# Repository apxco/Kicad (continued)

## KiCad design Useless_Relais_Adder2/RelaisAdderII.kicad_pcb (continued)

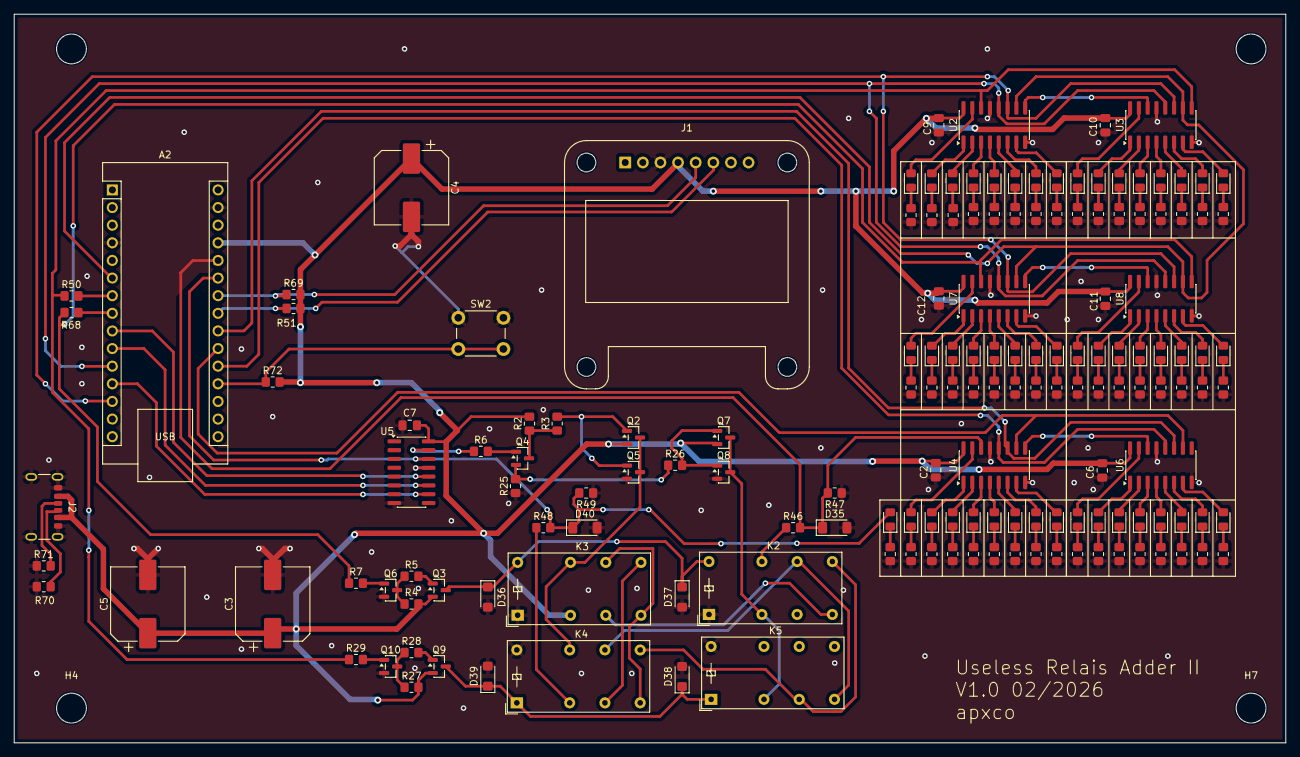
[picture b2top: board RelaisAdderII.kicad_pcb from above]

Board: 2 copper layers, 183.2 x 105.0 mm, 164 parts (0 on the bottom side), 145 nets.

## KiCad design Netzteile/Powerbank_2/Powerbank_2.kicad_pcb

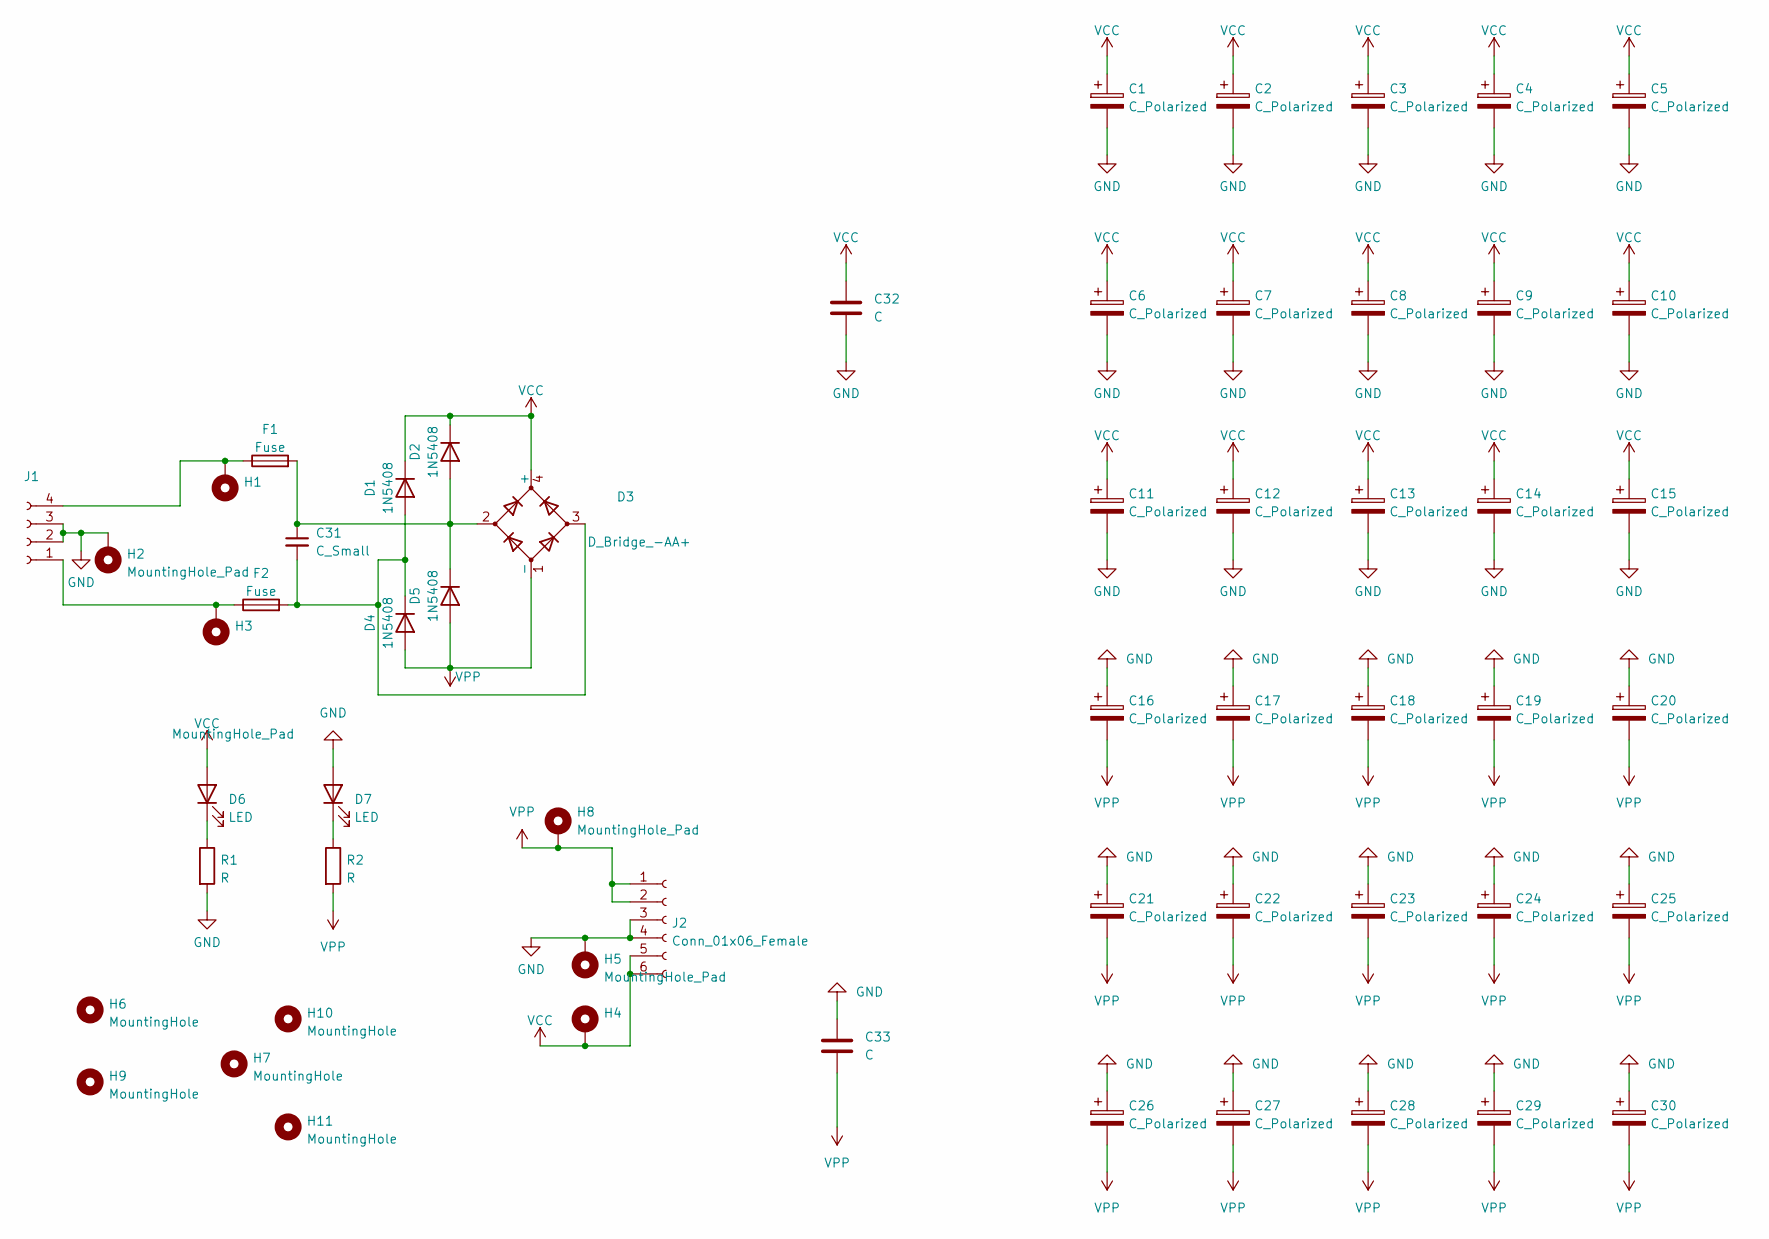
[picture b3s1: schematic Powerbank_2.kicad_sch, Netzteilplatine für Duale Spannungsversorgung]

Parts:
C1, C2, C3, C4, C5, C6, C7, C8, C9, C10, C11, C12, C13, C14, C15, C16, C17, C18, C19, C20, C21, C22, C23, C24, C25, C26, C27, C28, C29, C30: C_Polarized; CP_Radial_D10.0mm_P5.00mm_P7.50mm
C31: C_Small; C_Axial_L12.0mm_D6.5mm_P15.00mm_Horizontal
C32, C33: C; C_Rect_L16.5mm_W5.0mm_P15.00mm_MKT
D1, D2, D4, D5: 1N5408; D_DO-201AD_P15.24mm_Horizontal
D3: D_Bridge_-AA+; Diode_Bridge_Vishay_GBU
D6, D7: LED; LED_D3.0mm_Clear
F1, F2: Fuse; Fuseholder_Littelfuse_100_series_5x20mm
H1, H2, H3, H4, H5, H8: MountingHole_Pad; MountingHole_3.2mm_M3_Pad_TopBottom
H6, H7, H9, H10, H11: MountingHole; MountingHole_3.5mm_Pad
J1: Conn_01x04_Female; TerminalBlock_RND_205-00278_1x04_P5.00mm_Vertical
J2: Conn_01x06_Female; TerminalBlock_RND_205-00060_1x06_P5.00mm_45Degree
R1, R2: R; R_Axial_DIN0204_L3.6mm_D1.6mm_P7.62mm_Horizontal

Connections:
GND: C1.2, C2.2, C3.2, C4.2, C5.2, C6.2, C7.2, C8.2, C9.2, C10.2, C11.2, C12.2, C13.2, C14.2, C15.2, C16.1, C17.1, C18.1, C19.1, C20.1, C21.1, C22.1, C23.1, C24.1, C25.1, C26.1, C27.1, C28.1, C29.1, C30.1, C32.2, C33.1, D7.2 (A), H2.1, H5.1, J1.2, J1.3, J2.3, J2.4, R1.2
unnamed: C31.2, D1.2 (A), D3.3, D4.1 (K), F2.2
unnamed: C31.1, D2.2 (A), D3.2, D5.1 (K), F1.2
unnamed: D6.1 (K), R1.1
unnamed: D7.1 (K), R2.1
unnamed: F2.1, H3.1, J1.1
unnamed: F1.1, H1.1, J1.4
VCC: C1.1, C2.1, C3.1, C4.1, C5.1, C6.1, C7.1, C8.1, C9.1, C10.1, C11.1, C12.1, C13.1, C14.1, C15.1, C32.1, D1.1 (K), D2.1 (K), D3.4 (+), D6.2 (A), H4.1, J2.5, J2.6
VPP: C16.2, C17.2, C18.2, C19.2, C20.2, C21.2, C22.2, C23.2, C24.2, C25.2, C26.2, C27.2, C28.2, C29.2, C30.2, C33.2, D3.1 (-), D4.2 (A), D5.2 (A), H8.1, J2.1, J2.2, R2.2

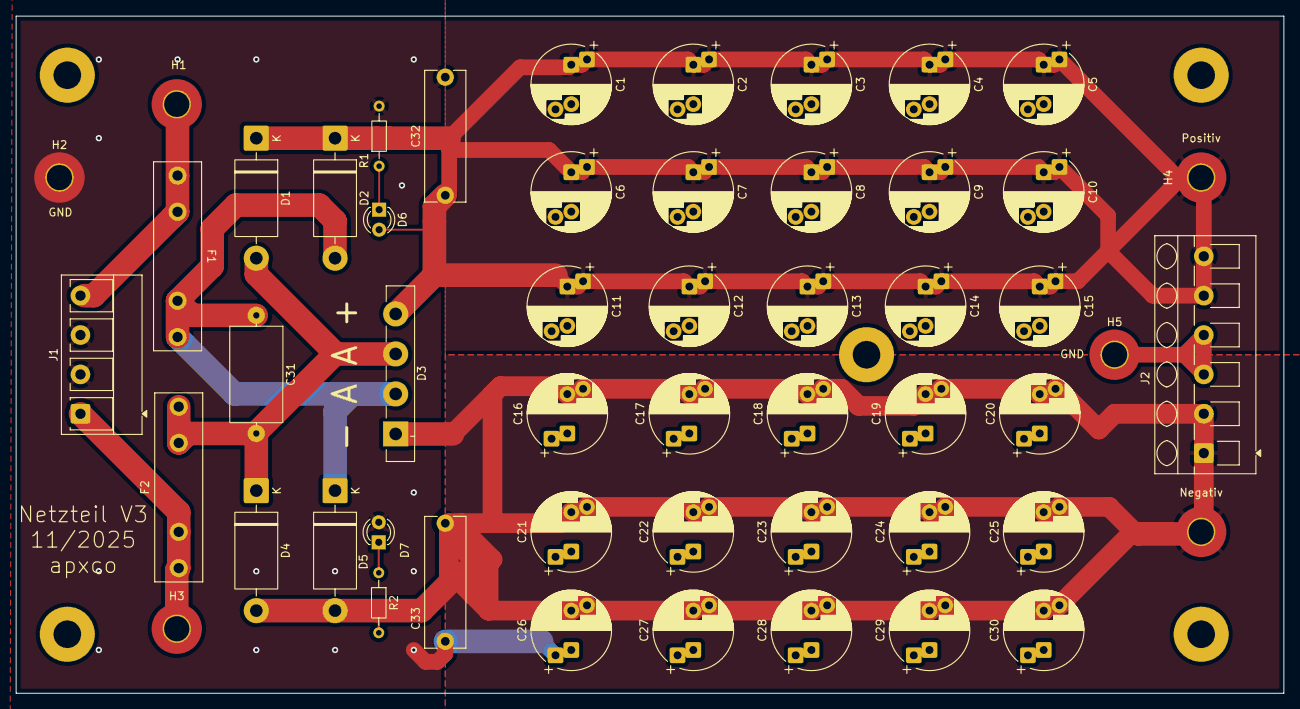
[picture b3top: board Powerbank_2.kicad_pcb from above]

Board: 2 copper layers, 161.0 x 86.0 mm, 57 parts (0 on the bottom side), 9 nets.

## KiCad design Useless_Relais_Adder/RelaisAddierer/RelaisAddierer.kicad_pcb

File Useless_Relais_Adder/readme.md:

Kombination aus Mikrocontroller und 8-Bit Relais Addierer.<br/>

yC übernimmt die Ansteuerung der beiden Daten Bytes, die über die Relais Addiert werden und sorgt für die Ausgabe.<br/>

https://www.youtube.com/watch?v=YAB79SiROqY

04.09.2025  Initiale Idee zum Projekt, Erstellung Schaltbild und Leiterplatte Version 1.0 <br/>
05.09.2025  Weiter an Leiterplatte, grobe Positionierung der Elemente, erste Schritte bei der Programmierung<br/>
06.09.2025  Bauteile zurecht gerückt, klappt nicht gut mit KiCad muss ich sagen.<br/>
07.09.2025  Layout steht soweit, keine wesentlichen Änderungen mehr vorgesehen an der Platine, jetzt Fehlersuche und Polieren.<br/>
08.09.2025  Fehlerkorrekturen im Layout. Wesentlich noch 3,3V zu 5V Pegelwandler für die GPIO Pins eingesetzt. Im Endstadium des Wahnsinns Platine bestellt, ab morgen Software <br/>
12.09.2025  vielleicht ab heute Software<br/>
23.9.2025 Platine Version 1.0 wurde geliefert, aufgebaut ohne Relais für Fehlersuche. Zu kleiner Fußabdruck bei den Freilaufdioden, Kurzschluss an den Multiplexern zwischen +5V und SDA, Ausgänge der Multiplexer empfindlich für statische Aufladung. Bauteilwerte scheinen OK zu sein soweit. Lötpasstenschablone ist scharfkantig.<br/>
20.10.2025 Nach der schmerzlichen Erkenntnis, dass nicht alle PiPico bords die gleiche Pinbelegung haben, gibt es einen Fortschritt bei der Programmierung. Kann den TCA9534 jetzt ohne zusätzliche Bibliotheken ansprechen, zumindest beim Schreiben. Ansteuerung der Relais funktioniert trotz Open Collector Ausgang.<br/>
21.10.2025 Platine Version 1.0 weitere Fehler bei der Relaisverschaltung, wird in Version 2.0 korrigiert. <br/>
23.10.2025 Soweit ist die SW fertig. Umsetzen der Ergebnis OK Anzeige mittels Inversion der Anzeige. Die verwendete Bibliothek kommt mit 2 Drehschaltern scheinbar nicht gut klar, immer einer der Schalter wird nicht richtig ausgewertet. Lasse es jetzt so, die Art der Bedienung, x10 wenn Druck auf SW1 für beide Bytes gefällt mir auch. Platine V2.0 Angefangen und erste Korrrekturen vorgenommen. Version 1.0 konnte ich mit zusätzlichen Leitungen zur Mitarbeit bewegen, funktioniert damit. Werde die Version 2.0 mit allen Korrekturen online stellen, aber nur Bestellen und Aufbauen wenn ich eine 2. Maschine baue. <br/>
24.10.2025 Ich definiere die Software als fertig. Für den Zufallsmodus werden die Eingangswerte in 10 Schritten nacheinander eingegeben, ganz witzig anzusehen. 
12.12.2025 Um ESD probleme in der Eingangsstufe zu vermeiden, Spannunsgteiler an den Eingängen eisetzt <br/>

Hintergrund:

Ob Röhren oder Relais, die alten Rechner und Steuerungen haben schon etwas faszinierendes. Das beweisen auch jede Menge Projekte auf YouTube oder im Netz in denen Leute erstaunliche Maschinen aus diesen alten Konzepten bauen. Den Nutzen der gebauten Maschine selbst, natürlich lernt man viel und hat Spaß beim Bauen, daran kann man aber zweifeln. Damit es hier keinen Zweifel gibt, die Idee ist hieraus eine Art Useless Maschine zu machen, ein schönes Stück für den Schreibtisch der ab und an Geräusche macht. Nebenbei ein wenig programmieren und möglichst ein paar Bauteile aus der Bastelkiste aufbrauchen.<br/>
<br/>

Erkenntnisse:

Trotz zusätzlich notwendiger Verbindungen auf der Rückseite, zu kleinen Pads und der nicht korrekten Ausgangsbeschaltung der TCA9534 funktioniert die Platine auf anhieb. Man muss einfach Glück haben.<br/>
Ich bin kein guter Programmierer. Python macht es jedem recht einfach auch sowas umzusetzen. Insbesondere die Programmierumgebung kommt einem solchen Projet sehr entgegen. Allerdings wird es schnell zeitkritisch bzw. Dinge die man gerne über Interupts lösen würde, gehen so nicht. Zumindest ich bekomme es nicht hin.<br/>

Für mein nächstes Projekt würde ich eine andere Spannungsversorgung vorsehen. Genaugenommen mag ich die Buchse nicht. USBC wäre eleganter und in dem Leistungsbereich möglich gewesen. Die maximal Stromaufnahme beträgt bei 12V um 1A. Die Schaltung funktioniert noch bis etwa 10V, danach gibt es rechenfehler durch faule Relais ;).<br/>

Es soll ja useless sein und damit ist Übertreibung sozusagen Teil des Spiels. Da aber noch Ports am PiPico frei sind, würde ich die Auswertung der Ausgangs Bytes über den PiPico direkt machen und nicht mehr über einen TCA9534. Spart kosten, macht die Schaltung einfacher und hat hier keinen Nachteil. Für das Carry Bit ist es hier sowieso so gemacht.

Für die genaue Umsetzung für mich einige Punkte zur Strukturierung der Aufgabe<br/>

Maximale Geschwindigkeit ist nicht erforderlich, es darf gemütlich zugehen.<br/>

Bedienung:<br/>

Drehgeber SW1 Byte A Wert 1x einstellen. Bei Druck auf SW1 10x <br/>

Drehgeber SW2 Byte B Wert einstellen. Bei Druck auf SW1 10x <br/>

3 Betriebsarten Normalbetrieb und Zufallsbetrieb<br/>

Tastendruck SW2: Daten Byte 1 und Byte 2 Werden eingeladen Berechnung startet, einmalig. Ohne weiteren Tastendruck läuft Timer für Zufallsbetrieb (wiederholend).  <br/>

Über das Display soll Byte A, Byte B und das Ergebnis als dezimale Werte Angezeigt werden. Ebenfalls ein optische Kontrolle Ergebnis korrekt/nicht korrekt.
Die Ergebnisanzeige und Kontrolle ist fortlaufend in beiden Betriebsarten.<br/>

Im Normalbetrieb werden die Werte Byte A und Byte B über die Drehgeber eingestellt, im Display angezeigt, auf Tastendruck SW2 werden die Daten an die Relais ausgegeben.<br/>

Bis zum Abschluss der Berechnung soll die Ergebnisanzeige ständig aktualisiert werden bis Datenübertagung abgeschlossen ist.<br/>

Im Zufallsbetrieb werden die Werte Byte A und Byte B durch den yC gesetzt, im Display angezeigt, und nacheinander augegeben <br/>

Bis zum Abschluss der Berechnung soll die Ergebnisanzeige ständig aktualisiert werden bis Datenübertagung abgeschlossen ist. Wiederholt sich nach kurzer Zeit.<br/>

<br/>

V1.0 Hack auf fast 2.0 ;-)

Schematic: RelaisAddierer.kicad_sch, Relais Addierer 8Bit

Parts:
A1: RaspberryPi_Pico; RaspberryPi_Pico_Common_Unspecified
C1: 1uF; C_0805_2012Metric_Pad1.18x1.45mm_HandSolder
C2, C3, C5, C6, C7, C201, C202: 100nF; C_0805_2012Metric_Pad1.18x1.45mm_HandSolder
C8, C9, C10, C11, C12: 470uF; CP_Elec_10x12.5
D2, D201, D202, D203, D204, D205, D206, D207, D208, D209, D210, D211, D212, D213, D214, D215, D216, D217, D218, D219, D220, D221, D222, D223, D224, D225, D226, D227, D228, D229, D230, D231, D232: 1N4148WT; D_SMF
D9: 1N4007; D_DO-41_SOD81_P10.16mm_Horizontal
D34, D35, D36, D37, D38, D39, D40, D41, D43, D44, D45, D46, D47, D48, D49, D50, D59, D60, D61, D62, D63, D64, D65, D66, D67: LED; LED_0805_2012Metric_Pad1.15x1.40mm_HandSolder
D51, D52, D53, D54, D55, D56, D57, D58: BZD27C47; D_MiniMELF
H2, H3, H4, H5, H6, H7: MountingHole; MountingHole_4.3mm_M4_DIN965
J1: Conn_01x08_Pin; PinHeader_1x08_P2.54mm_Vertical
J2: Barrel_Jack; BarrelJack_GCT_DCJ200-10-A_Horizontal
K201, K202, K203, K204, K205, K206, K207, K208, K209, K210, K211, K212, K213, K214, K215, K216, K217, K218, K219, K220, K221, K222, K223, K224, K225, K226, K227, K228, K229, K230, K231, K232: HK19F-DCxxV-SHC; Relay_DPDT_Finder_30.22
Q1, Q2, Q3, Q4, Q5, Q7, Q8, Q10, Q17, Q18, Q19, Q20, Q21, Q23, Q24, Q26: BC847; SOT-23
Q6: PJM10H01PSA; SOT-23
Q9, Q11, Q12, Q13, Q14, Q15, Q16, Q22, Q25, Q27, Q28, Q29, Q30, Q31, Q32: DMP3099L; SOT-23
Q201, Q202: BSS138; SOT-23
R1, R2, R3, R4, R5, R6, R15, R17, R19, R22, R25, R27, R29, R31, R48, R50, R52, R55, R58, R60, R62, R64, R201, R202, R203, R204: 10k; R_0805_2012Metric_Pad1.20x1.40mm_HandSolder
R7, R8, R9, R10, R35, R36, R37, R38, R39, R40, R41, R42, R43, R68, R69, R70, R71, R72, R73, R74, R75, R76, R77, R78, R79, R80, R81, R82, R84, R85, R86, R87, R88, R89, R90, R91, R92, R93, R94, R95, R96: 1k; R_0805_2012Metric_Pad1.20x1.40mm_HandSolder
R11, R12, R13, R14, R16, R18, R20, R21, R23, R24, R26, R28, R30, R32, R33, R34, R44, R45, R46, R47, R49, R51, R53, R54, R56, R57, R59, R61, R63, R65, R66, R67: 100R; R_0805_2012Metric_Pad1.20x1.40mm_HandSolder
R83: 560; R_0805_2012Metric_Pad1.20x1.40mm_HandSolder
R205: 2,6k; R_0805_2012Metric_Pad1.20x1.40mm_HandSolder
SW1, SW2: RotaryEncoder_Switch; RotaryEncoder_Alps_EC12E-Switch_Vertical_H20mm
U1, U2, U3: TCA9534; TSSOP-16_4.4x5mm_P0.65mm
U4: uA7805; TO-263-2

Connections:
+3.3V: A1.36 (3V3), C201.1, C202.1, D2.1 (K), Q201.1 (G), Q202.1 (G), R1.1, R2.2, R3.2, R4.1, R5.2, R6.2, R201.2, R203.2
+5V: A1.40 (VBUS), C2.1, C3.1, C5.1, C6.1, C7.1, C12.1, J1.4, R202.2, R204.2, U1.16 (VDD), U2.1 (A0), U2.16 (VDD), U3.2 (A1), U3.16 (VDD), U4.3 (OUT)
+12V: C1.1, C8.1, C9.1, C10.1, C11.1, D9.1 (K), K201.11, K202.11, K203.11, K205.11, K207.11, K210.11, K217.11, K219.11, K221.11, K223.11, Q6.2 (S), Q9.2 (S), Q11.2 (S), Q12.2 (S), Q13.2 (S), Q14.2 (S), Q15.2 (S), Q16.2 (S), Q22.2 (S), Q25.2 (S), Q27.2 (S), Q28.2 (S), Q29.2 (S), Q30.2 (S), Q31.2 (S), Q32.2 (S), R15.2, R17.2, R19.2, R22.2, R25.2, R27.2, R29.2, R31.2, R48.2, R50.2, R52.2, R55.2, R58.2, R60.2, R62.2, R64.2, U4.1 (IN)
Bit A.1: D43.2 (A), D201.1 (K), D204.1 (K), K201.A2, K202.A2, Q22.3 (D)
Bit A.2: D44.2 (A), D205.1 (K), D208.1 (K), K203.A2, K204.A2, Q25.3 (D)
Bit A.3: D45.2 (A), D202.1 (K), D206.1 (K), K205.A2, K206.A2, Q27.3 (D)
Bit A.4: D46.2 (A), D203.1 (K), D207.1 (K), K207.A2, K208.A2, Q28.3 (D)
Bit A.5: D47.2 (A), D217.1 (K), D221.1 (K), K217.A2, K218.A2, Q29.3 (D)
Bit A.6: D48.2 (A), D220.1 (K), D224.1 (K), K219.A2, K220.A2, Q30.3 (D)
Bit A.7: D49.2 (A), D218.1 (K), D222.1 (K), K221.A2, K222.A2, Q31.3 (D)
Bit A.8: D50.2 (A), D219.1 (K), D223.1 (K), K223.A2, K224.A2, Q32.3 (D)
Bit B.1: D34.2 (A), D209.1 (K), D210.1 (K), K209.A1, K210.A1, Q6.3 (D)
Bit B.2: D35.2 (A), D213.1 (K), D216.1 (K), K211.A1, K212.A1, Q9.3 (D)
Bit B.3: D36.2 (A), D211.1 (K), D214.1 (K), K213.A1, K214.A1, Q11.3 (D)
Bit B.4: D37.2 (A), D212.1 (K), D215.1 (K), K215.A1, K216.A1, Q12.3 (D)
Bit B.5: D38.2 (A), D225.1 (K), D226.1 (K), K225.A1, K226.A1, Q13.3 (D)
Bit B.6: D39.2 (A), D229.1 (K), D232.1 (K), K227.A1, K228.A1, Q14.3 (D)
Bit B.7: D40.2 (A), D227.1 (K), D230.1 (K), K229.A1, K230.A1, Q15.3 (D)
Bit B.8: D41.2 (A), D228.1 (K), D231.1 (K), K231.A1, K232.A1, Q16.3 (D)
CLK1: A1.21 (GPIO16), R1.2, SW1.A
CLK2: A1.24 (GPIO18), R4.2, SW2.A
Carry_Bit1: K203.21, K209.11, K211.21
Carry_Bit1_neg: K204.11, K210.21, K212.11
Carry_Bit2: K205.21, K211.11, K213.21
Carry_Bit2_neg: K206.11, K212.21, K214.11
Carry_Bit3: K207.21, K213.11, K215.21
Carry_Bit3_neg: K208.11, K214.21, K216.11
Carry_Bit4: K215.11, K217.21, K225.21
Carry_Bit4_neg: K216.21, K218.11, K226.11
Carry_Bit5: K219.21, K225.11, K227.21
Carry_Bit5_neg: K220.11, K226.21, K228.11
Carry_Bit6: K221.21, K227.11, K229.21
Carry_Bit6_neg: K222.11, K228.21, K230.11
Carry_Bit7: K223.21, K229.11, K231.21
Carry_Bit7_neg: K224.11, K230.21, K232.11
Carry_Bit8: D59.2 (A), K231.11, R205.1
DT1: A1.22 (GPIO17), R2.1, SW1.B
DT2: A1.25 (GPIO19), R5.1, SW2.B
GND: A1.3 (GND), A1.8 (GND), A1.13 (GND), A1.18 (GND), A1.23 (GND), A1.28 (GND), A1.33 (AGND), A1.38 (GND), C1.2, C2.2, C3.2, C5.2, C6.2, C7.2, C8.2, C9.2, C10.2, C11.2, C12.2, C201.2, C202.2, D51.2 (A), D52.2 (A), D53.2 (A), D54.2 (A), D55.2 (A), D56.2 (A), D57.2 (A), D58.2 (A), D201.2 (A), D202.2 (A), D203.2 (A), D204.2 (A), D205.2 (A), D206.2 (A), D207.2 (A), D208.2 (A), D209.2 (A), D210.2 (A), D211.2 (A), D212.2 (A), D213.2 (A), D214.2 (A), D215.2 (A), D216.2 (A), D217.2 (A), D218.2 (A), D219.2 (A), D220.2 (A), D221.2 (A), D222.2 (A), D223.2 (A), D224.2 (A), D225.2 (A), D226.2 (A), D227.2 (A), D228.2 (A), D229.2 (A), D230.2 (A), D231.2 (A), D232.2 (A), J1.3, J2.2, K201.A1, K202.A1, K203.A1, K204.A1, K205.A1, K206.A1, K207.A1, K208.A1, K209.A2, K210.A2, K211.A2, K212.A2, K213.A2, K214.A2, K215.A2, K216.A2, K217.A1, K218.A1, K219.A1, K220.A1, K221.A1, K222.A1, K223.A1, K224.A1, K225.A2, K226.A2, K227.A2, K228.A2, K229.A2, K230.A2, K231.A2, K232.A2, Q1.2 (E), Q2.2 (E), Q3.2 (E), Q4.2 (E), Q5.2 (E), Q7.2 (E), Q8.2 (E), Q10.2 (E), Q17.2 (E), Q18.2 (E), Q19.2 (E), Q20.2 (E), Q21.2 (E), Q23.2 (E), Q24.2 (E), Q26.2 (E), R7.1, R8.1, R9.1, R10.1, R35.2, R36.2, R37.2, R38.2, R39.2, R40.2, R41.2, R42.2, R43.1, R68.2, R69.2, R70.2, R71.2, R72.2, R73.2, R74.2, R75.2, R84.2, R85.2, R86.2, R87.2, R88.2, R89.2, R90.2, R91.2, R92.2, R93.1, R94.1, R95.1, R96.1, SW1.C, SW1.S2, SW2.C, SW2.S2, U1.1 (A0), U1.2 (A1), U1.3 (A2), U1.8 (GND), U2.2 (A1), U2.3 (A2), U2.8 (GND), U3.1 (A0), U3.3 (A2), U3.8 (GND), U4.2 (GND)
I2C0 SCL: J1.5, Q202.3 (D), R204.1, U1.14 (SCL), U2.14 (SCL), U3.14 (SCL)
I2C0 SDA: J1.6, Q201.3 (D), R202.1, U1.15 (SDA), U2.15 (SDA), U3.15 (SDA)
unnamed: A1.20 (GPIO15), D2.2 (A), R43.2, R205.2
unnamed: A1.26 (GPIO20), Q201.2 (S), R201.1
unnamed: A1.27 (GPIO21), Q202.2 (S), R203.1
unnamed: D9.2 (A), J2.1
unnamed: D34.1 (K), R35.1
unnamed: D35.1 (K), R36.1
unnamed: D36.1 (K), R37.1
unnamed: D37.1 (K), R38.1
unnamed: D38.1 (K), R39.1
unnamed: D39.1 (K), R40.1
unnamed: D40.1 (K), R41.1
unnamed: D41.1 (K), R42.1
unnamed: D43.1 (K), R68.1
unnamed: D44.1 (K), R69.1
unnamed: D45.1 (K), R70.1
unnamed: D46.1 (K), R71.1
unnamed: D47.1 (K), R72.1
unnamed: D48.1 (K), R73.1
unnamed: D49.1 (K), R74.1
unnamed: D50.1 (K), R75.1
unnamed: D51.1 (K), R7.2, R76.1, U3.4 (P0)
unnamed: D52.1 (K), R77.1, R96.2, U3.12 (P7)
unnamed: D53.1 (K), R8.2, R78.1, U3.5 (P1)
unnamed: D54.1 (K), R79.1, R95.2, U3.11 (P6)
unnamed: D55.1 (K), R9.2, R80.1, U3.6 (P2)
unnamed: D56.1 (K), R81.1, R94.2, U3.10 (P5)
unnamed: D57.1 (K), R10.2, R82.1, U3.7 (P3)
unnamed: D58.1 (K), R83.1, R93.2, U3.9 (P4)
unnamed: D59.1 (K), R84.1
unnamed: D60.1 (K), R85.1
unnamed: D61.1 (K), R86.1
unnamed: D62.1 (K), R87.1
unnamed: D63.1 (K), R88.1
unnamed: D64.1 (K), R89.1
unnamed: D65.1 (K), R90.1
unnamed: D66.1 (K), R91.1
unnamed: D67.1 (K), R92.1
unnamed: K201.12, K202.14, K210.22
unnamed: K201.14, K201.22, K209.14
unnamed: K201.24, K209.12
unnamed: K202.12, K210.24
unnamed: K202.22, K210.14
unnamed: K202.24, K210.12
unnamed: K203.12, K204.14, K212.22
unnamed: K203.14, K203.22, K211.14
unnamed: K203.24, K211.12
unnamed: K204.12, K212.24
unnamed: K204.22, K211.22, K212.14
unnamed: K204.24, K211.24, K212.12
unnamed: K205.12, K206.14
unnamed: K205.14, K205.22, K213.14
unnamed: K205.24, K213.12
unnamed: K206.22, K213.22, K214.14
unnamed: K206.24, K213.24, K214.12
unnamed: K207.12, K208.14, K216.22
unnamed: K207.14, K207.22, K215.14
unnamed: K207.24, K215.12
unnamed: K208.12, K216.24
unnamed: K208.22, K215.22, K216.14
unnamed: K208.24, K215.24, K216.12
unnamed: K217.12, K218.14, K226.22
unnamed: K217.14, K217.22, K225.14
unnamed: K217.24, K225.12
unnamed: K218.12, K226.24
unnamed: K218.22, K225.22, K226.14
unnamed: K218.24, K225.24, K226.12
unnamed: K219.12, K220.14, K228.22
unnamed: K219.14, K219.22, K227.14
unnamed: K219.24, K227.12
unnamed: K220.12, K228.24
unnamed: K220.22, K227.22, K228.14
unnamed: K220.24, K227.24, K228.12
unnamed: K221.12, K222.14, K230.22
unnamed: K221.14, K221.22, K229.14
unnamed: K221.24, K229.12
unnamed: K222.12, K230.24
unnamed: K222.22, K229.22, K230.14
unnamed: K222.24, K229.24, K230.12
unnamed: K223.12, K224.14
unnamed: K223.14, K223.22, K231.14
unnamed: K223.24, K231.12
unnamed: K224.22, K231.22, K232.14
unnamed: K224.24, K231.24, K232.12
unnamed: Q1.1 (B), R11.2
unnamed: Q1.3 (C), R15.1, R20.1
unnamed: Q2.1 (B), R12.2
unnamed: Q2.3 (C), R17.1, R23.1
unnamed: Q3.1 (B), R13.2
unnamed: Q3.3 (C), R19.1, R26.1
unnamed: Q4.1 (B), R14.2
unnamed: Q4.3 (C), R22.1, R28.1
unnamed: Q5.1 (B), R16.2
unnamed: Q5.3 (C), R25.1, R30.1
unnamed: Q6.1 (G), R20.2
unnamed: Q7.1 (B), R18.2
unnamed: Q7.3 (C), R27.1, R32.1
unnamed: Q8.1 (B), R21.2
unnamed: Q8.3 (C), R29.1, R33.1
unnamed: Q9.1 (G), R23.2
unnamed: Q10.1 (B), R24.2
unnamed: Q10.3 (C), R31.1, R34.1
unnamed: Q11.1 (G), R26.2
unnamed: Q12.1 (G), R28.2
unnamed: Q13.1 (G), R30.2
unnamed: Q14.1 (G), R32.2
unnamed: Q15.1 (G), R33.2
unnamed: Q16.1 (G), R34.2
unnamed: Q17.1 (B), R44.2
unnamed: Q17.3 (C), R48.1, R53.1
unnamed: Q18.1 (B), R45.2
unnamed: Q18.3 (C), R50.1, R56.1
unnamed: Q19.1 (B), R46.2
unnamed: Q19.3 (C), R52.1, R59.1
unnamed: Q20.1 (B), R47.2
unnamed: Q20.3 (C), R55.1, R61.1
unnamed: Q21.1 (B), R49.2
unnamed: Q21.3 (C), R58.1, R63.1
unnamed: Q22.1 (G), R53.2
unnamed: Q23.1 (B), R51.2
unnamed: Q23.3 (C), R60.1, R65.1
unnamed: Q24.1 (B), R54.2
unnamed: Q24.3 (C), R62.1, R66.1
unnamed: Q25.1 (G), R56.2
unnamed: Q26.1 (B), R57.2
unnamed: Q26.3 (C), R64.1, R67.1
unnamed: Q27.1 (G), R59.2
unnamed: Q28.1 (G), R61.2
unnamed: Q29.1 (G), R63.2
unnamed: Q30.1 (G), R65.2
unnamed: Q31.1 (G), R66.2
unnamed: Q32.1 (G), R67.2
unnamed: R44.1, U1.4 (P0)
unnamed: R45.1, U1.5 (P1)
unnamed: R46.1, U1.6 (P2)
unnamed: R47.1, U1.7 (P3)
unnamed: R49.1, U1.9 (P4)
unnamed: R51.1, U1.10 (P5)
unnamed: R54.1, U1.11 (P6)
unnamed: R57.1, U1.12 (P7)
unnamed: R11.1, U2.4 (P0)
unnamed: R12.1, U2.5 (P1)
unnamed: R13.1, U2.6 (P2)
unnamed: R14.1, U2.7 (P3)
unnamed: R16.1, U2.9 (P4)
unnamed: R18.1, U2.10 (P5)
unnamed: R21.1, U2.11 (P6)
unnamed: R24.1, U2.12 (P7)
SW1: A1.29 (GPIO22), R3.1, SW1.S1
SW2: A1.31 (GPIO26_ADC0), R6.1, SW2.S1
Summ_Bit1: D67.2 (A), K202.21, R76.2
Summ_Bit2: D66.2 (A), K204.21, R78.2
Summ_Bit3: D65.2 (A), K206.21, R80.2
Summ_Bit4: D64.2 (A), K208.21, R82.2
Summ_Bit5: D63.2 (A), K218.21, R83.2
Summ_Bit6: D62.2 (A), K220.21, R81.2
Summ_Bit7: D61.2 (A), K222.21, R79.2
Summ_Bit8: D60.2 (A), K224.21, R77.2

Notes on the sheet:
Eingang Ergebnis Bit
Netzteil
0x21
Byte A
0x22
Byte B
Byte A
Ergebnis Eingang
Ausgang Byte B
Display
0x20
SSD11306 i2c
Ausgang Byte A
0x3c
Relais HK19F-DC12V-SHG Spule 12V 12,5mA bis 30mA Stromaufnahme Benötigt 32 Relais Netzteil 12 V bei 20mA Mittlerer Stromaufnahme und 32 Relais 640mA

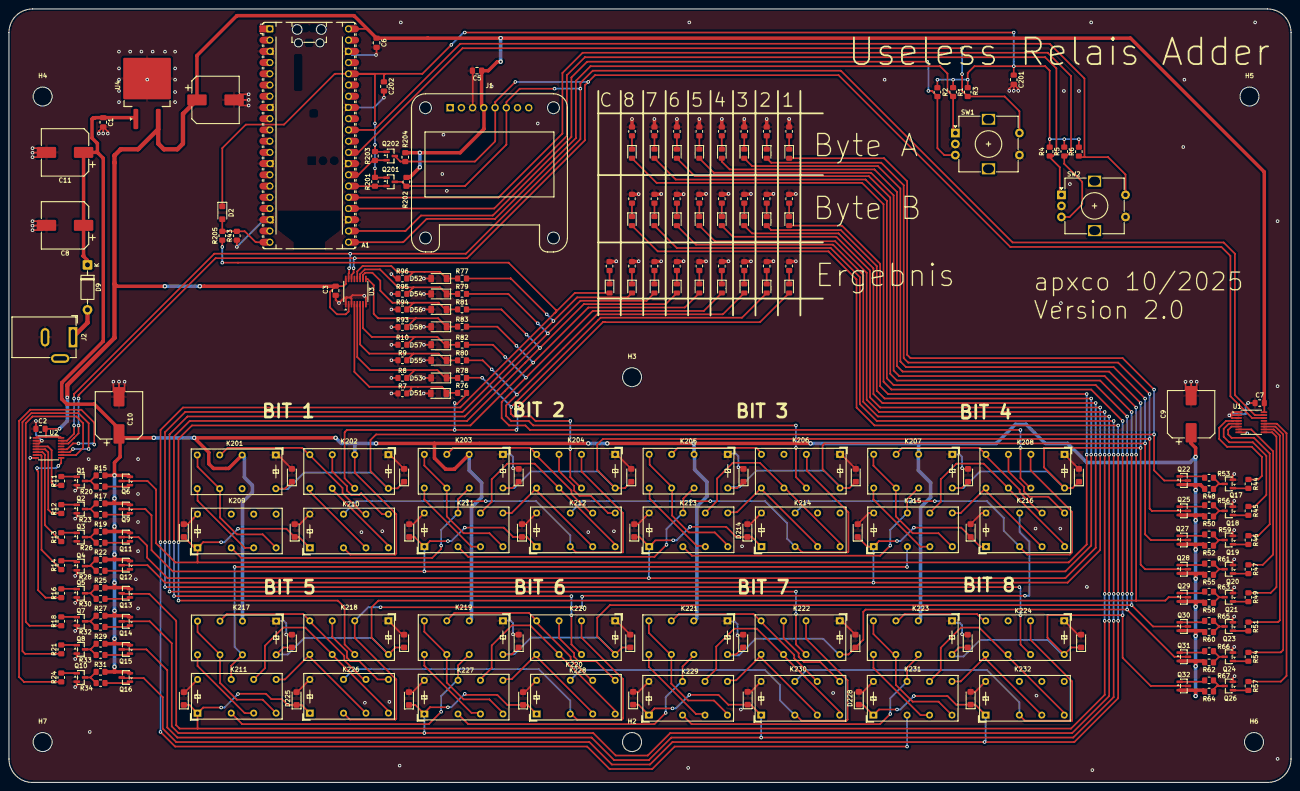
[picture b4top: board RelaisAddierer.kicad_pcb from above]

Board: 2 copper layers, 290.1 x 175.0 mm, 262 parts (0 on the bottom side), 198 nets.

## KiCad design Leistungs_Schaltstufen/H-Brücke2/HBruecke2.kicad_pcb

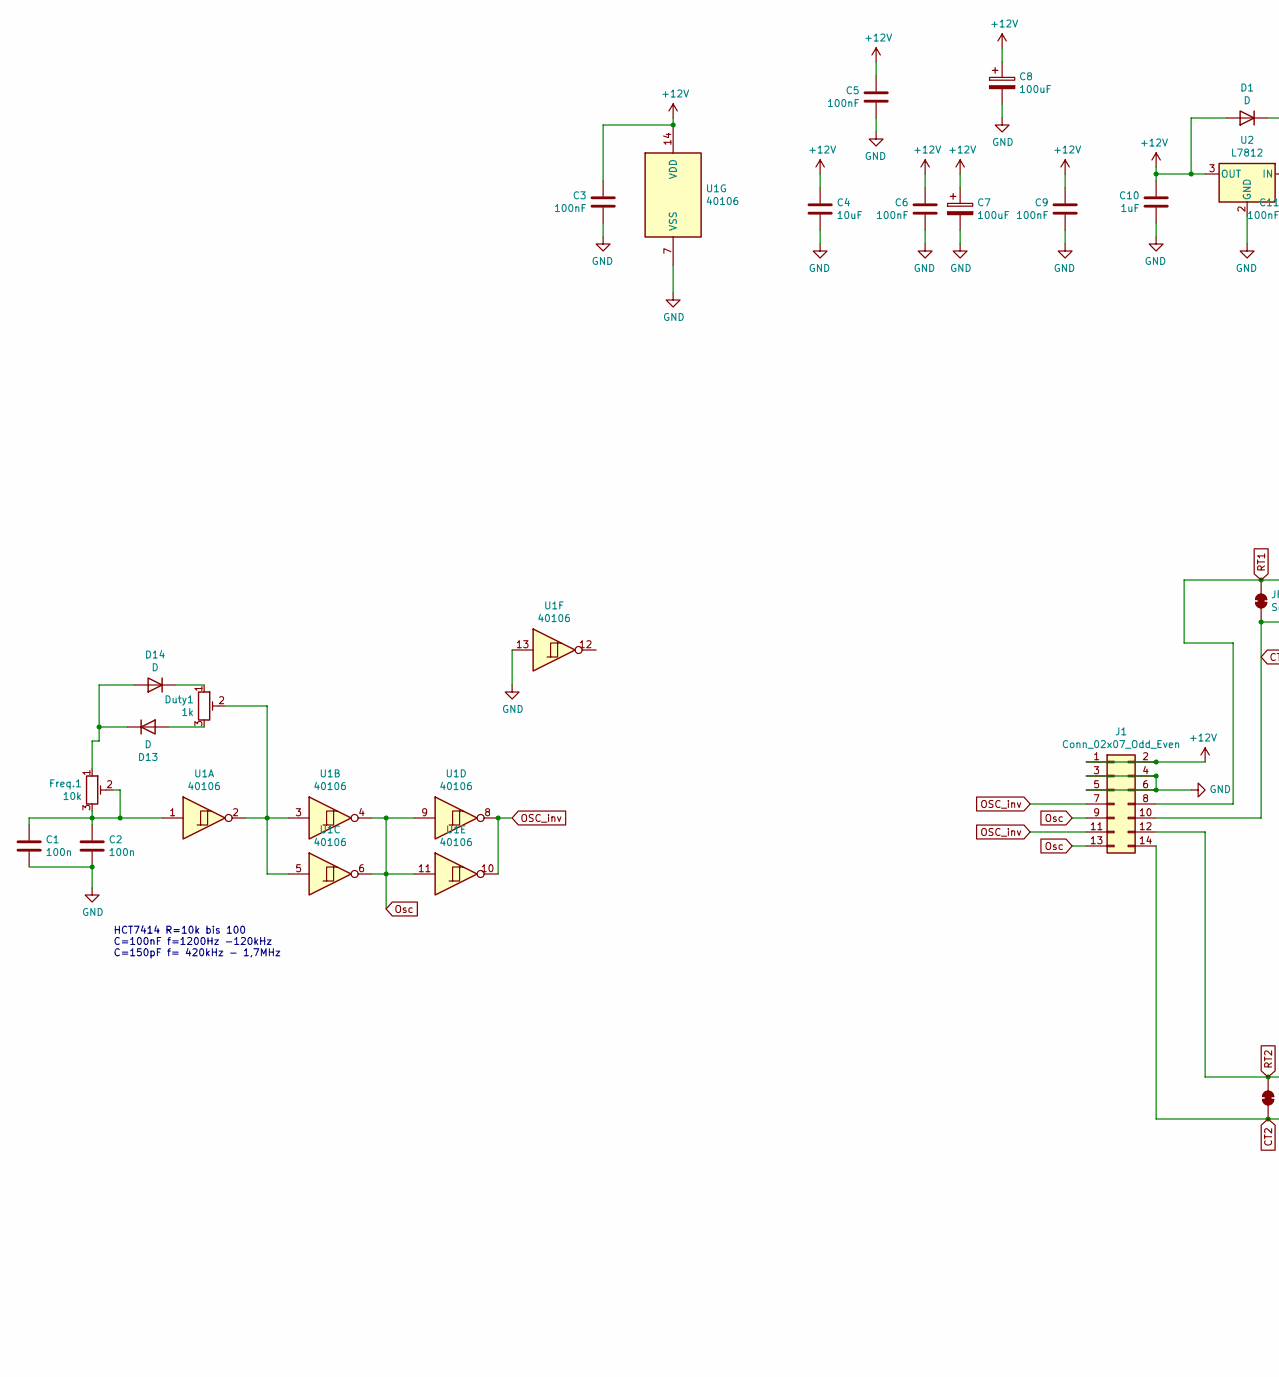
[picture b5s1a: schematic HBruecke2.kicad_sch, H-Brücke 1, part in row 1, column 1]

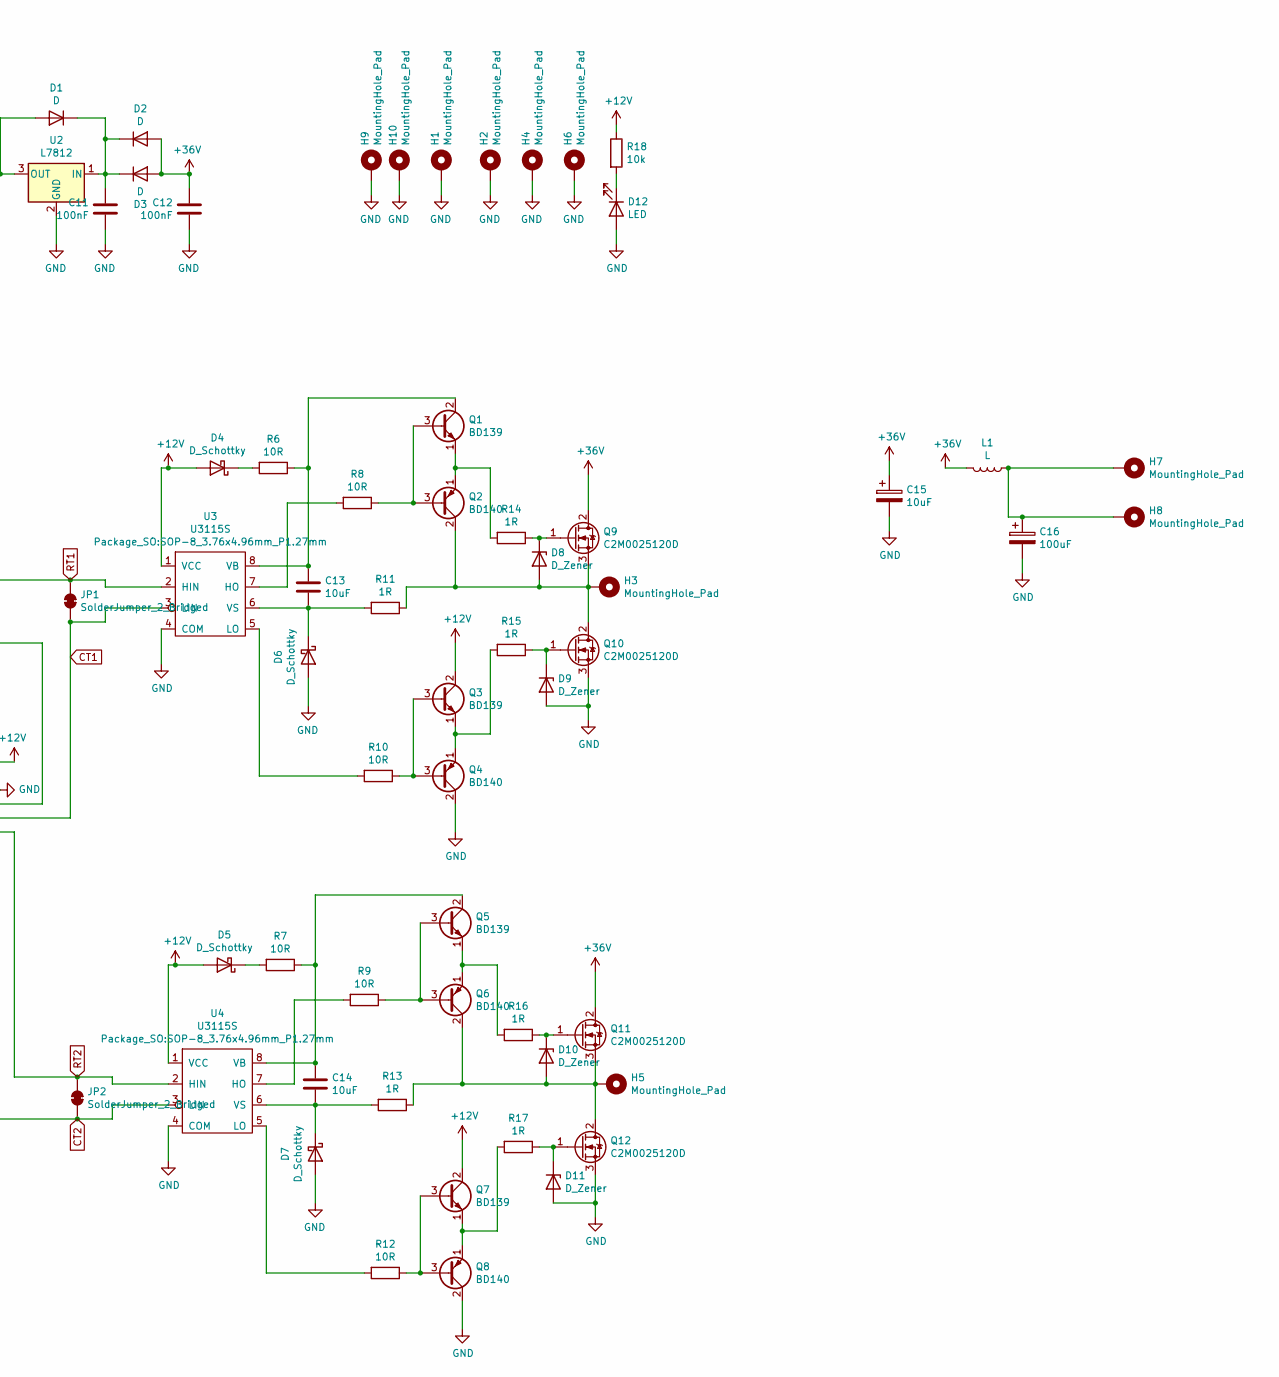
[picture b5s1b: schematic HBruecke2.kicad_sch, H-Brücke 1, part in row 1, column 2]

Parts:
C1: 100n; C_Axial_L3.8mm_D2.6mm_P7.50mm_Horizontal
C2: 100n; C_0805_2012Metric_Pad1.18x1.45mm_HandSolder
C3, C5, C6: 100nF; C_0805_2012Metric_Pad1.18x1.45mm_HandSolder
C4, C14: 10uF; C_1210_3225Metric_Pad1.33x2.70mm_HandSolder
C7, C8: 100uF; CP_Elec_10x10.5
C9, C11, C12: 100nF; C_0805_2012Metric_Pad1.15x1.40mm_HandSolder
C10: 1uF; C_0805_2012Metric_Pad1.15x1.40mm_HandSolder
C13: 10uF; C_1210_3225Metric_Pad1.42x2.65mm_HandSolder
C15: 10uF; C_Rect_L28.0mm_W10.0mm_P22.50mm_MKS4
C16: 100uF; CP_Radial_D22.0mm_P10.00mm_SnapIn
D1, D13, D14: D; D_0805_2012Metric_Pad1.15x1.40mm_HandSolder
D2: D; D_A-405_P7.62mm_Horizontal
D3: D; D_SOD-123
D4, D5, D6, D7: D_Schottky; D_SOD-123
D8, D9, D10, D11: D_Zener; D_SOD-123
D12: LED; LED_0805_2012Metric_Pad1.15x1.40mm_HandSolder
Duty1: 1k; Potentiometer_Bourns_3296W_Vertical
Freq.1: 10k; Potentiometer_Bourns_3296W_Vertical
H1, H2: MountingHole_Pad; MountingHole_3.2mm_M3_DIN965_Pad
H3, H4, H5, H6, H7, H8: MountingHole_Pad; MountingHole_2.5mm_Pad_Via
H9, H10: MountingHole_Pad; TestPoint_THTPad_D2.5mm_Drill1.2mm
J1: Conn_02x07_Odd_Even; PinHeader_2x07_P2.54mm_Vertical
JP1, JP2: SolderJumper_2_Bridged; SolderJumper-2_P1.3mm_Open_RoundedPad1.0x1.5mm
L1: L; L_Toroid_Vertical_L16.3mm_W7.1mm_P7.11mm_Pulse_H
Q1, Q3, Q5, Q7: BD139; TO-126-3_Vertical
Q2, Q4, Q6, Q8: BD140; TO-126-3_Vertical
Q9, Q10, Q11, Q12: C2M0025120D; TO-247-3_Vertical
R6, R7, R8, R9, R10, R12: 10R; R_0805_2012Metric_Pad1.20x1.40mm_HandSolder
R11, R13, R14, R15, R16, R17: 1R; R_1206_3216Metric_Pad1.30x1.75mm_HandSolder
R18: 10k; R_0805_2012Metric_Pad1.20x1.40mm_HandSolder
U1: 40106; SO-14_3.9x8.65mm_P1.27mm
U2: L7812; TO-252-2
U3, U4: U3115S; SOP-8_3.76x4.96mm_P1.27mm

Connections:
+12V: C3.1, C4.1, C5.1, C6.1, C7.1, C8.1, C9.1, C10.1, D1.2 (A), D4.2 (A), D5.2 (A), J1.1, J1.2, Q3.2 (C), Q7.2 (C), R18.1, U1.14 (VDD), U2.3 (OUT), U3.1 (VCC), U4.1 (VCC)
+36V: C12.1, C15.1, D2.2 (A), D3.2 (A), L1.2, Q9.2 (D), Q11.2 (D)
CT1: J1.10, JP1.2 (B), U3.3 (LIN)
CT2: J1.14, JP2.2 (B), U4.3 (LIN)
GND: C1.2, C2.2, C3.2, C4.2, C5.2, C6.2, C7.2, C8.2, C9.2, C10.2, C11.2, C12.2, C15.2, C16.2, D6.2 (A), D7.2 (A), D9.2 (A), D11.2 (A), D12.2 (A), H1.1, H2.1, H4.1, H6.1, H9.1, H10.1, J1.3, J1.4, J1.5, J1.6, Q4.2 (C), Q8.2 (C), Q10.3 (S), Q12.3 (S), U1.7 (VSS), U1.13, U2.2 (GND), U3.4 (COM), U4.4 (COM)
unnamed: C1.1, C2.1, Freq.1.2, Freq.1.3, U1.1
unnamed: C11.1, D1.1 (K), D2.1 (K), D3.1 (K), U2.1 (IN)
unnamed: C13.1, Q1.2 (C), R6.1, U3.8 (VB)
unnamed: C13.2, D6.1 (K), R11.2, U3.6 (VS)
unnamed: C14.1, Q5.2 (C), R7.1, U4.8 (VB)
unnamed: C14.2, D7.1 (K), R13.2, U4.6 (VS)
unnamed: C16.1, H7.1, H8.1, L1.1
unnamed: D4.1 (K), R6.2
unnamed: D5.1 (K), R7.2
unnamed: D8.1 (K), Q9.1 (G), R14.1
unnamed: D8.2 (A), H3.1, Q2.2 (C), Q9.3 (S), Q10.2 (D), R11.1
unnamed: D9.1 (K), Q10.1 (G), R15.1
unnamed: D10.1 (K), Q11.1 (G), R16.1
unnamed: D10.2 (A), H5.1, Q6.2 (C), Q11.3 (S), Q12.2 (D), R13.1
unnamed: D11.1 (K), Q12.1 (G), R17.1
unnamed: D12.1 (K), R18.2
unnamed: D13.1 (K), D14.2 (A), Freq.1.1
unnamed: D13.2 (A), Duty1.3
unnamed: D14.1 (K), Duty1.1
unnamed: Duty1.2, U1.2, U1.3, U1.5
unnamed: Q1.1 (E), Q2.1 (E), R14.2
unnamed: Q1.3 (B), Q2.3 (B), R8.1
unnamed: Q3.1 (E), Q4.1 (E), R15.2
unnamed: Q3.3 (B), Q4.3 (B), R10.1
unnamed: Q5.1 (E), Q6.1 (E), R16.2
unnamed: Q5.3 (B), Q6.3 (B), R9.1
unnamed: Q7.1 (E), Q8.1 (E), R17.2
unnamed: Q7.3 (B), Q8.3 (B), R12.1
unnamed: R8.2, U3.7 (HO)
unnamed: R9.2, U4.7 (HO)
unnamed: R10.2, U3.5 (LO)
unnamed: R12.2, U4.5 (LO)
OSC_inv: J1.7, J1.11, U1.8, U1.10
Osc: J1.9, J1.13, U1.4, U1.6, U1.9, U1.11
RT1: J1.8, JP1.1 (A), U3.2 (HIN)
RT2: J1.12, JP2.1 (A), U4.2 (HIN)

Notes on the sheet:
HCT7414 R=10k bis 100 C=100nF f=1200Hz -120kHz C=150pF f= 420kHz - 1,7MHz

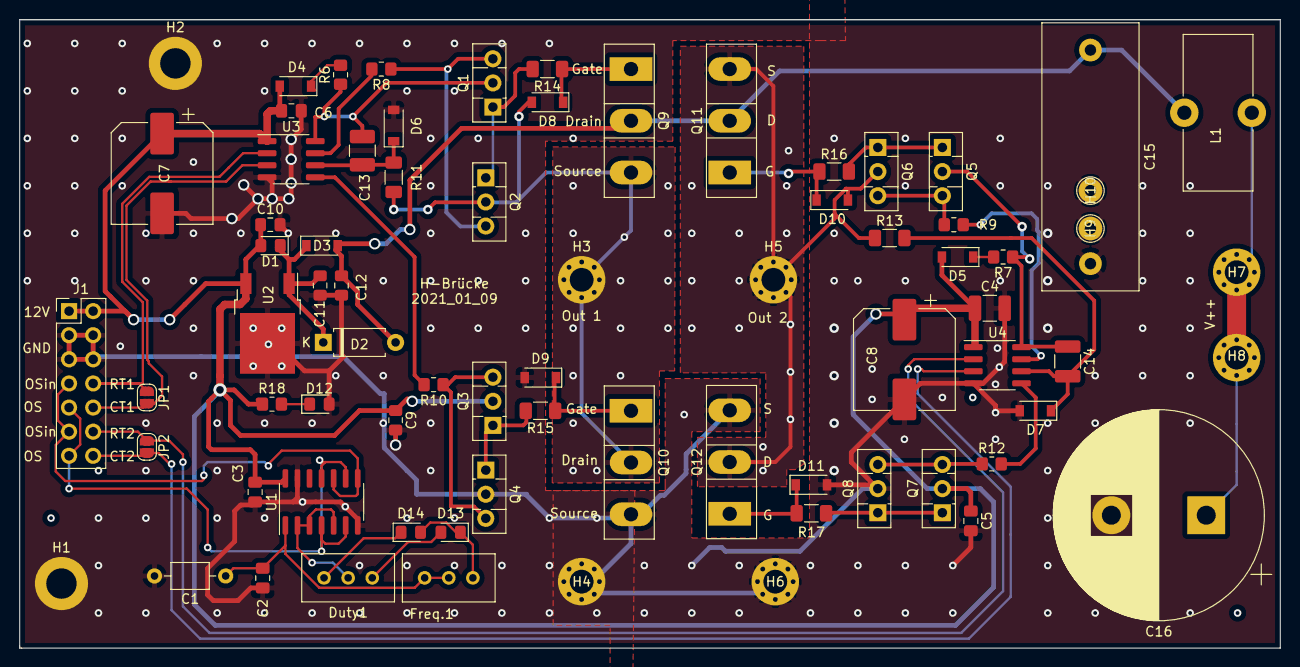
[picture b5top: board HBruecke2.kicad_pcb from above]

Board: 2 copper layers, 132.8 x 66.2 mm, 75 parts (0 on the bottom side), 41 nets.
